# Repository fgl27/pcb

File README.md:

# pcb

This is a collection of PCBs prototypes for projects that I have created off participated.

If anything here help you enjoy it.

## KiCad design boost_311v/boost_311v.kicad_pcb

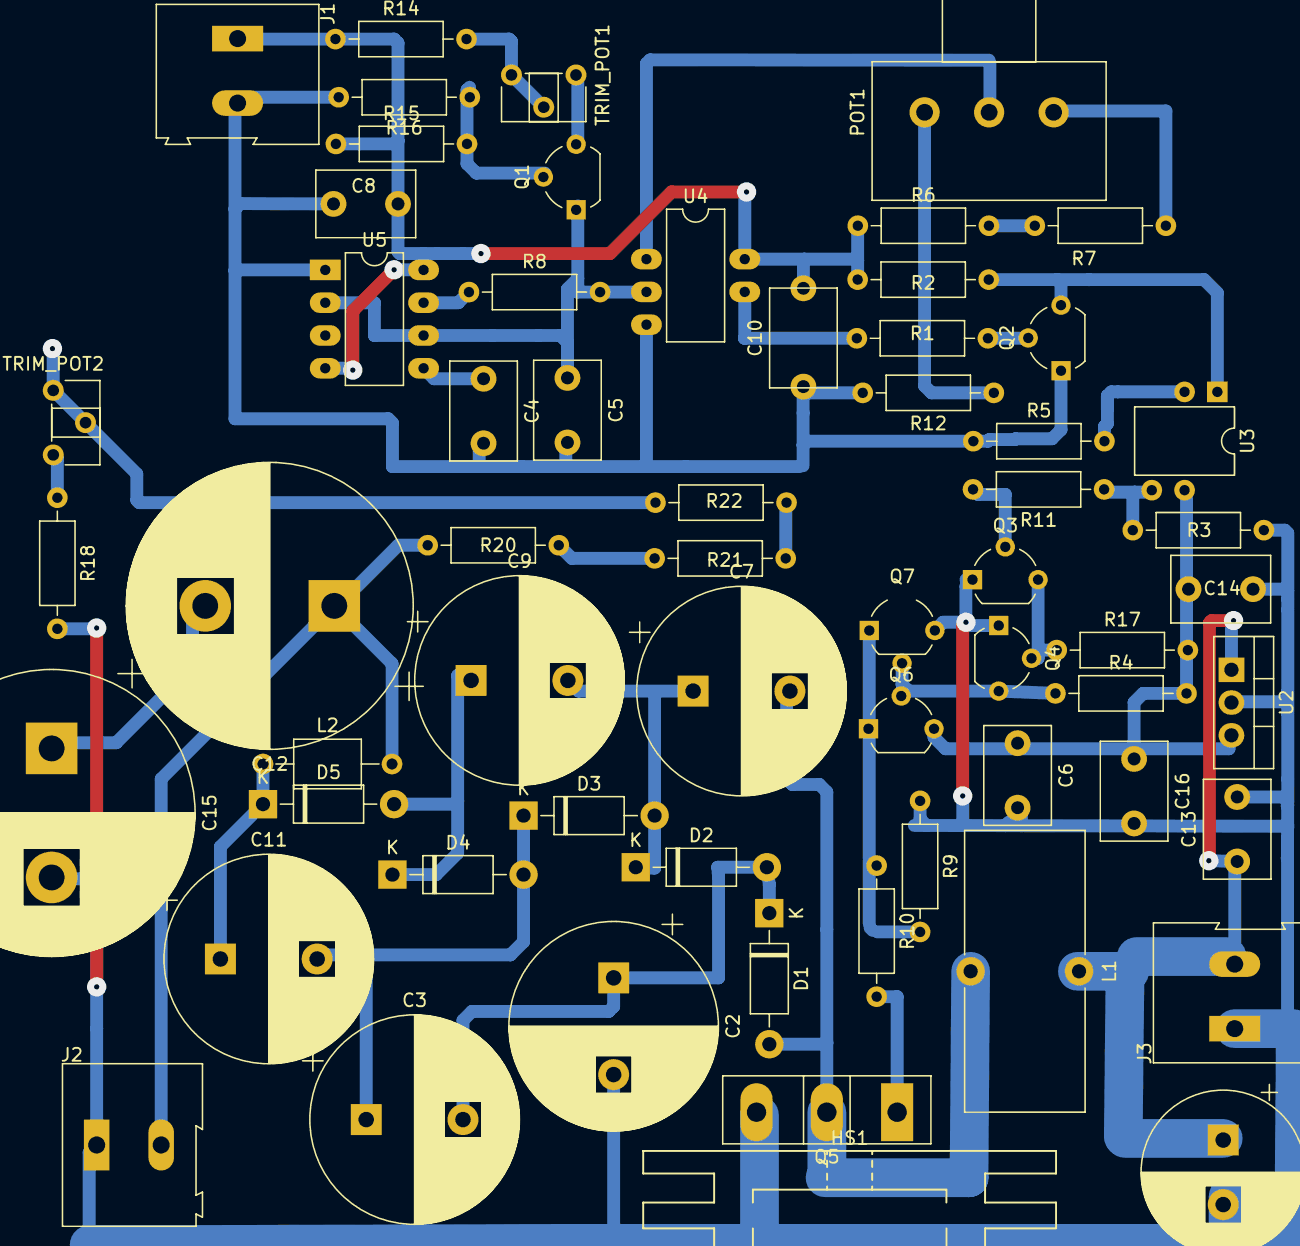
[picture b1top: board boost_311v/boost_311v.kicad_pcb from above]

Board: 2 copper layers, 61 parts (0 on the bottom side), 37 nets.

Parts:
C1: 100µF; CP_Radial_D12.5mm_P5.00mm
C2: 100µF; CP_Radial_D16.0mm_P7.50mm
C3, C7, C9, C11: 100µF_200V; CP_Radial_D16.0mm_P7.50mm
C4: 10nF; C_Disc_D7.5mm_W5.0mm_P5.00mm
C5: 500pF; C_Disc_D7.5mm_W5.0mm_P5.00mm
C6, C8, C10, C14, C16: 100nF; C_Disc_D7.5mm_W5.0mm_P5.00mm
C12, C15: 200µF_200V; CP_Radial_D22.0mm_P10.00mm_SnapIn
C13: 10µF; C_Disc_D7.5mm_W5.0mm_P5.00mm
D1, D2, D3, D4, D5: FR154; D_DO-41_SOD81_P10.16mm_Horizontal
HS1: Heatsink; Heatsink_Stonecold_HS-132_32x14mm_2xFixation1.5mm
J1: Vin_cnt; TerminalBlock_Altech_AK300-2_P5.00mm
J2: VO; TerminalBlock_Altech_AK300-2_P5.00mm
J3: Vin_boost; TerminalBlock_Altech_AK300-2_P5.00mm
L1: 20µH; L_Toroid_Vertical_L21.6mm_W9.1mm_P8.40mm_Bourns_5700
L2: 100µ; L_Axial_L5.0mm_D3.6mm_P10.00mm_Horizontal_Murata_BL01RN1A2A2
POT1: 200kΩ; Potentiometer_Alps_RK163_Single_Horizontal
Q1: BC556; TO-92_Wide
Q2, Q3, Q4: PN2222A; TO-92_Wide
Q5: IRFP260; TO-247-3_Vertical
Q6: 2N3904; TO-92_Wide
Q7: 2N3906; TO-92_Wide
R1, R2, R4, R14: 1kΩ; R_Axial_DIN0207_L6.3mm_D2.5mm_P10.16mm_Horizontal
R3, R8: 330Ω; R_Axial_DIN0207_L6.3mm_D2.5mm_P10.16mm_Horizontal
R5: 470Ω; R_Axial_DIN0207_L6.3mm_D2.5mm_P10.16mm_Horizontal
R6, R7, R16, R18: 100kΩ; R_Axial_DIN0207_L6.3mm_D2.5mm_P10.16mm_Horizontal
R9, R11, R15, R17: 10kΩ; R_Axial_DIN0207_L6.3mm_D2.5mm_P10.16mm_Horizontal
R10: 47Ω; R_Axial_DIN0207_L6.3mm_D2.5mm_P10.16mm_Horizontal
R12: 80kΩ; R_Axial_DIN0207_L6.3mm_D2.5mm_P10.16mm_Horizontal
R20, R21: 330kΩ; R_Axial_DIN0207_L6.3mm_D2.5mm_P10.16mm_Horizontal
R22: 220kΩ; R_Axial_DIN0207_L6.3mm_D2.5mm_P10.16mm_Horizontal
TRIM_POT1, TRIM_POT2: 22kΩ; Potentiometer_ACP_CA6-H2,5_Horizontal
U2: L7812; TO-220-3_Vertical
U3: 4N25; DIP-6_W7.62mm
U4: LF357; DIP-8_W7.62mm_LongPads
U5: NE555; DIP-8_W7.62mm_LongPads

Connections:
+12V: C8.1, C10.2, J1.2, R2.2, R6.1, R14.1, R15.1, U4.7, U5.4, U5.8
+24V: C1.1, C13.1, J3.2, L1.1, U2.1
/10%_VO: R22.2, TRIM_POT2.1, TRIM_POT2.2
/12V_L7812: C6.1, C14.1, C16.1, Q6.3, R4.2, R17.2, U2.3, U3.5
/F_Serra: C5.1, Q1.1, R8.2, U4.3, U5.2, U5.6
/MOS_Gate: Q6.1, Q7.1, R9.2, R10.1
/PWM: Q2.3, R2.1, U3.1
GND: C4.2, C5.2, C8.2, C10.1, J1.1, Q2.1, R5.1, R12.2, R16.2, U4.4, U5.1
GNDA: C1.2, C2.2, C6.2, C13.2, C14.2, C15.2, C16.2, J2.2, J3.1, Q3.1, Q4.1, Q5.3, Q7.3, R3.1, R9.1, R18.2, U2.2
unnamed: C2.1, C3.2, D1.2, D2.1
unnamed: C4.1, U5.5
unnamed: C7.1, C9.2, D2.2, D3.1
unnamed: C7.2, D1.1, L1.2, Q5.2
unnamed: C9.1, D4.2, D5.1
unnamed: C11.1, D5.2, L2.1
unnamed: C3.1, C11.2, D3.2, D4.1
unnamed: C12.1, J2.1, L2.2, R20.1
unnamed: C12.2, C15.1
unnamed: POT1.1, R7.2
unnamed: POT1.2, U4.2
unnamed: POT1.3, R12.1
unnamed: Q1.2, R15.2, R16.1
unnamed: Q1.3, TRIM_POT1.3
unnamed: Q2.2, R1.2
unnamed: Q3.2, R11.2
unnamed: Q3.3, Q4.2, R17.1
unnamed: Q4.3, Q6.2, Q7.2, R4.1
unnamed: Q5.1, R10.2
unnamed: R1.1, U4.6
unnamed: R5.2, U3.2
unnamed: R6.2, R7.1
unnamed: R8.1, U5.7
unnamed: R3.2, R11.1, U3.4
unnamed: R14.2, TRIM_POT1.1, TRIM_POT1.2
unnamed: R18.1, TRIM_POT2.3
unnamed: R20.2, R21.1
unnamed: R21.2, R22.1

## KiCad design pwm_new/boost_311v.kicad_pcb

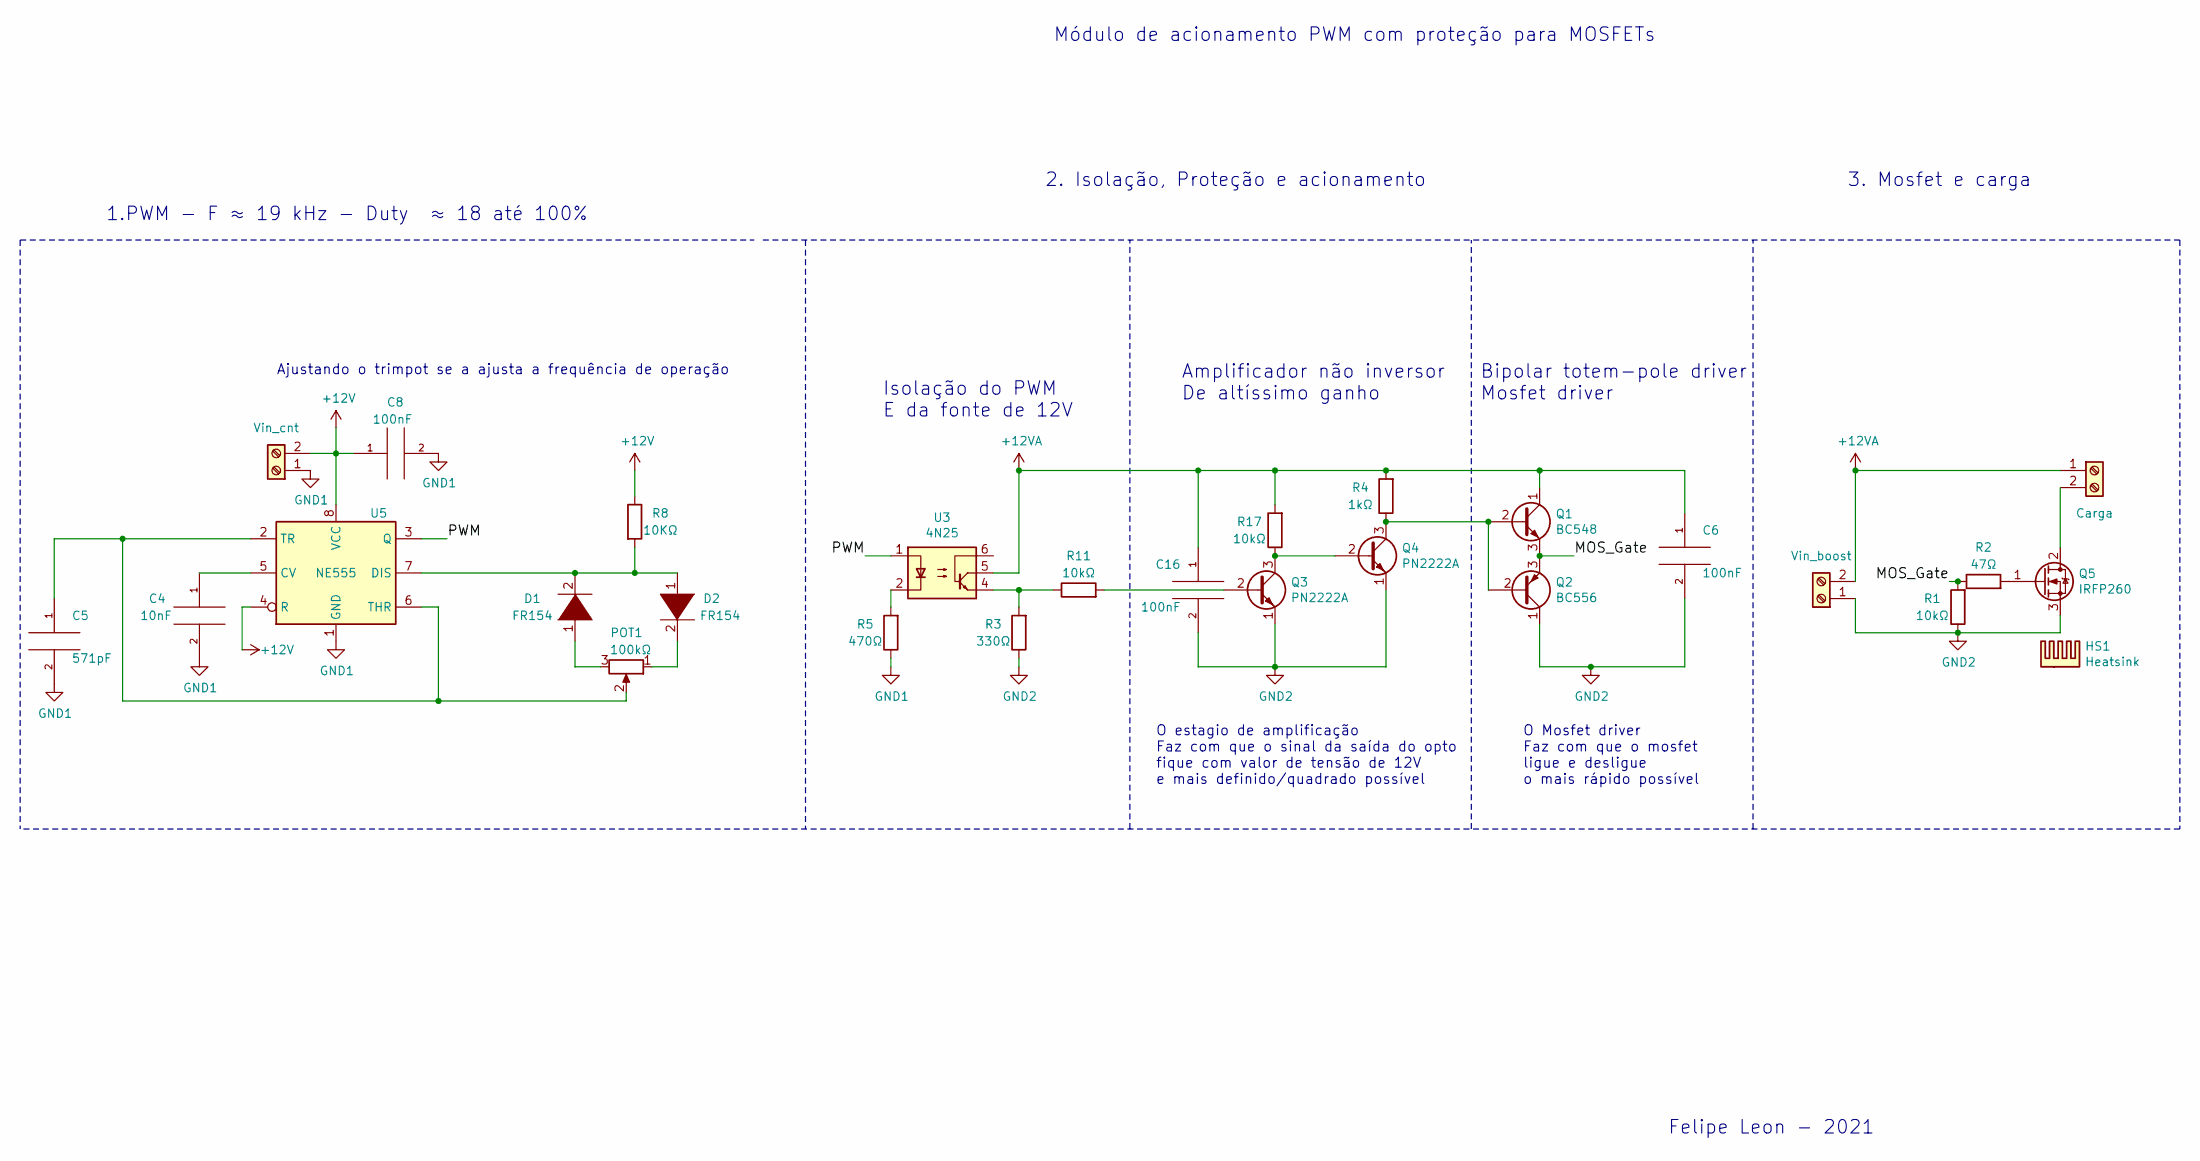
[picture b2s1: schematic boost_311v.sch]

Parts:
C4: 10nF; C_Disc_D7.5mm_W5.0mm_P5.00mm
C5: 571pF; C_Disc_D7.5mm_W5.0mm_P5.00mm
C6, C8, C16: 100nF; C_Disc_D7.5mm_W5.0mm_P5.00mm
D1, D2: FR154; D_DO-41_SOD81_P10.16mm_Horizontal
HS1: Heatsink; Heatsink_Stonecold_HS-132_32x14mm_2xFixation1.5mm
J1: Vin_cnt; TerminalBlock_Altech_AK300-2_P5.00mm
J2: Carga; TerminalBlock_Altech_AK300-2_P5.00mm
J3: Vin_boost; TerminalBlock_Altech_AK300-2_P5.00mm
POT1: 100kΩ; Potentiometer_Alps_RK163_Single_Horizontal
Q1: BC548; TO-92_Wide
Q2: BC556; TO-92_Wide
Q3, Q4: PN2222A; TO-92_Wide
Q5: IRFP260; TO-247-3_Vertical
R1, R11, R17: 10kΩ; R_Axial_DIN0207_L6.3mm_D2.5mm_P10.16mm_Horizontal
R2: 47Ω; R_Axial_DIN0207_L6.3mm_D2.5mm_P10.16mm_Horizontal
R3: 330Ω; R_Axial_DIN0207_L6.3mm_D2.5mm_P10.16mm_Horizontal
R4: 1kΩ; R_Axial_DIN0207_L6.3mm_D2.5mm_P10.16mm_Horizontal
R5: 470Ω; R_Axial_DIN0207_L6.3mm_D2.5mm_P10.16mm_Horizontal
R8: 10KΩ; R_Axial_DIN0207_L6.3mm_D2.5mm_P10.16mm_Horizontal
U3: 4N25; DIP-6_W7.62mm
U5: NE555; DIP-8_W7.62mm_LongPads

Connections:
+12V: C8.1, J1.2, R8.1, U5.4 (R), U5.8 (VCC)
+12VA: C6.1, C16.1, J2.1, J3.2, Q1.1 (C), R4.2, R17.2, U3.5
/MOS_Gate: Q1.3 (E), Q2.3 (E), R1.2, R2.1
/PWM: U3.1, U5.3 (Q)
GND1: C4.2, C5.2, C8.2, J1.1, R5.1, U5.1 (GND)
GND2: C6.2, C16.2, J3.1, Q2.1 (C), Q3.1 (E), Q4.1 (E), Q5.3 (S), R1.1, R3.1
unnamed: C4.1, U5.5 (CV)
unnamed: C5.1, POT1.2, U5.2 (TR), U5.6 (THR)
unnamed: D1.1 (K), POT1.3
unnamed: D1.2 (A), D2.1 (K), R8.2, U5.7 (DIS)
unnamed: D2.2 (A), POT1.1
unnamed: J2.2, Q5.2 (D)
unnamed: Q1.2 (B), Q2.2 (B), Q4.3 (C), R4.1
unnamed: Q3.2 (B), R11.2
unnamed: Q3.3 (C), Q4.2 (B), R17.1
unnamed: Q5.1 (G), R2.2
unnamed: R5.2, U3.2
unnamed: R3.2, R11.1, U3.4

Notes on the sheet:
1.PWM - F ≈ 19 kHz - Duty ≈ 18 até 100%
Ajustando o trimpot se a ajusta a frequência de operação
Felipe Leon - 2021
Isolação do PWM E da fonte de 12V
Amplificador não inversor De altíssimo ganho
Bipolar totem-pole driver Mosfet driver
O estagio de amplificação Faz com que o sinal da saída do opto fique com valor de tensão de 12V e mais definido/quadrado possível
O Mosfet driver Faz com que o mosfet ligue e desligue o mais rápido possível
3. Mosfet e carga
Módulo de acionamento PWM com proteção para MOSFETs
2. Isolação, Proteção e acionamento

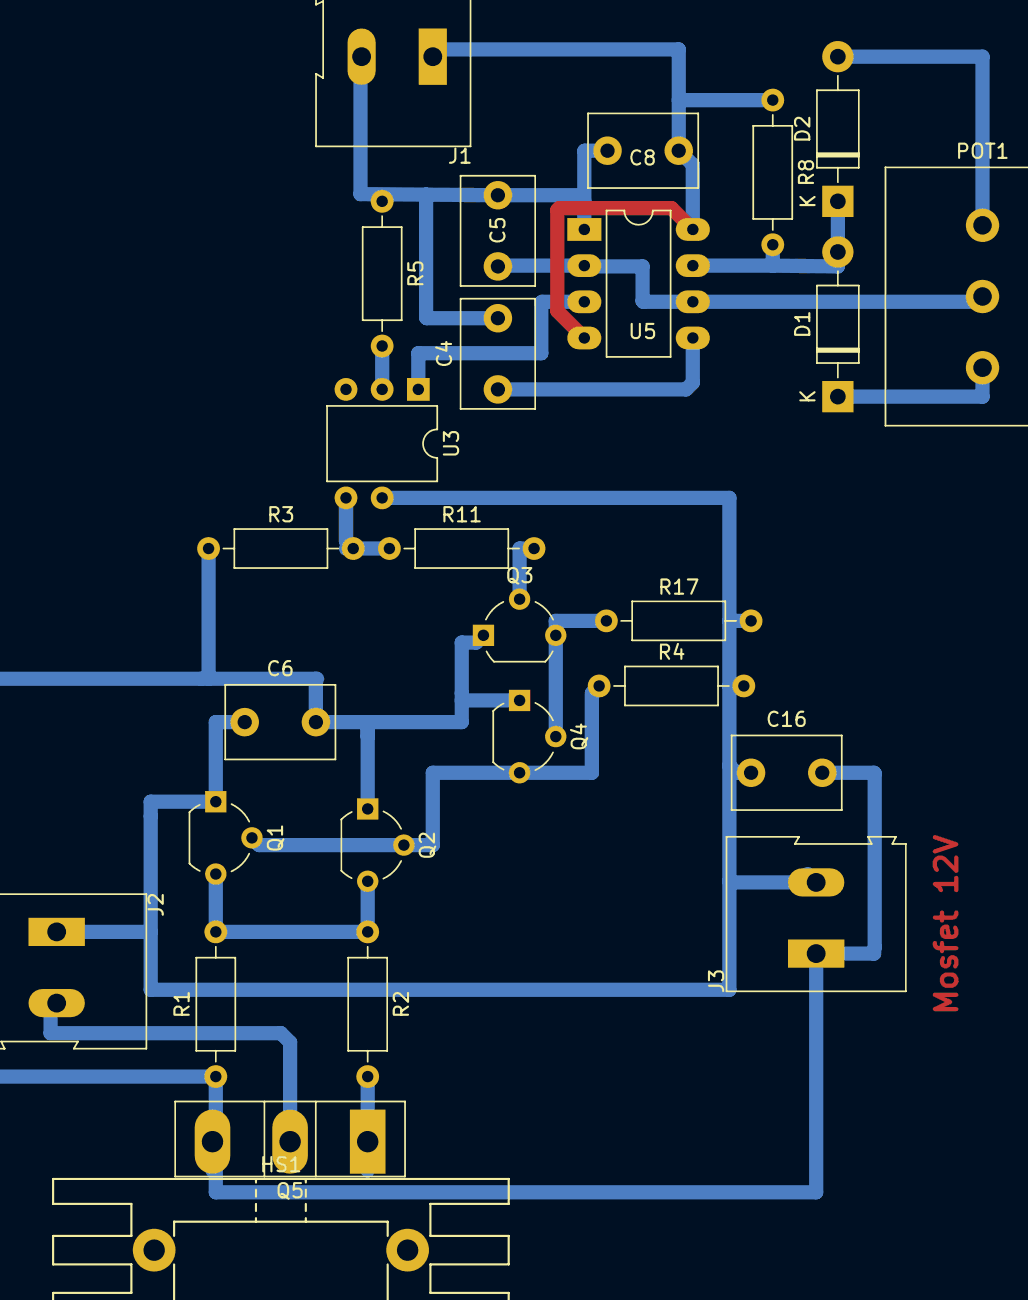
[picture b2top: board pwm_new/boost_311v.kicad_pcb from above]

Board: 2 copper layers, 27 parts (0 on the bottom side), 18 nets.

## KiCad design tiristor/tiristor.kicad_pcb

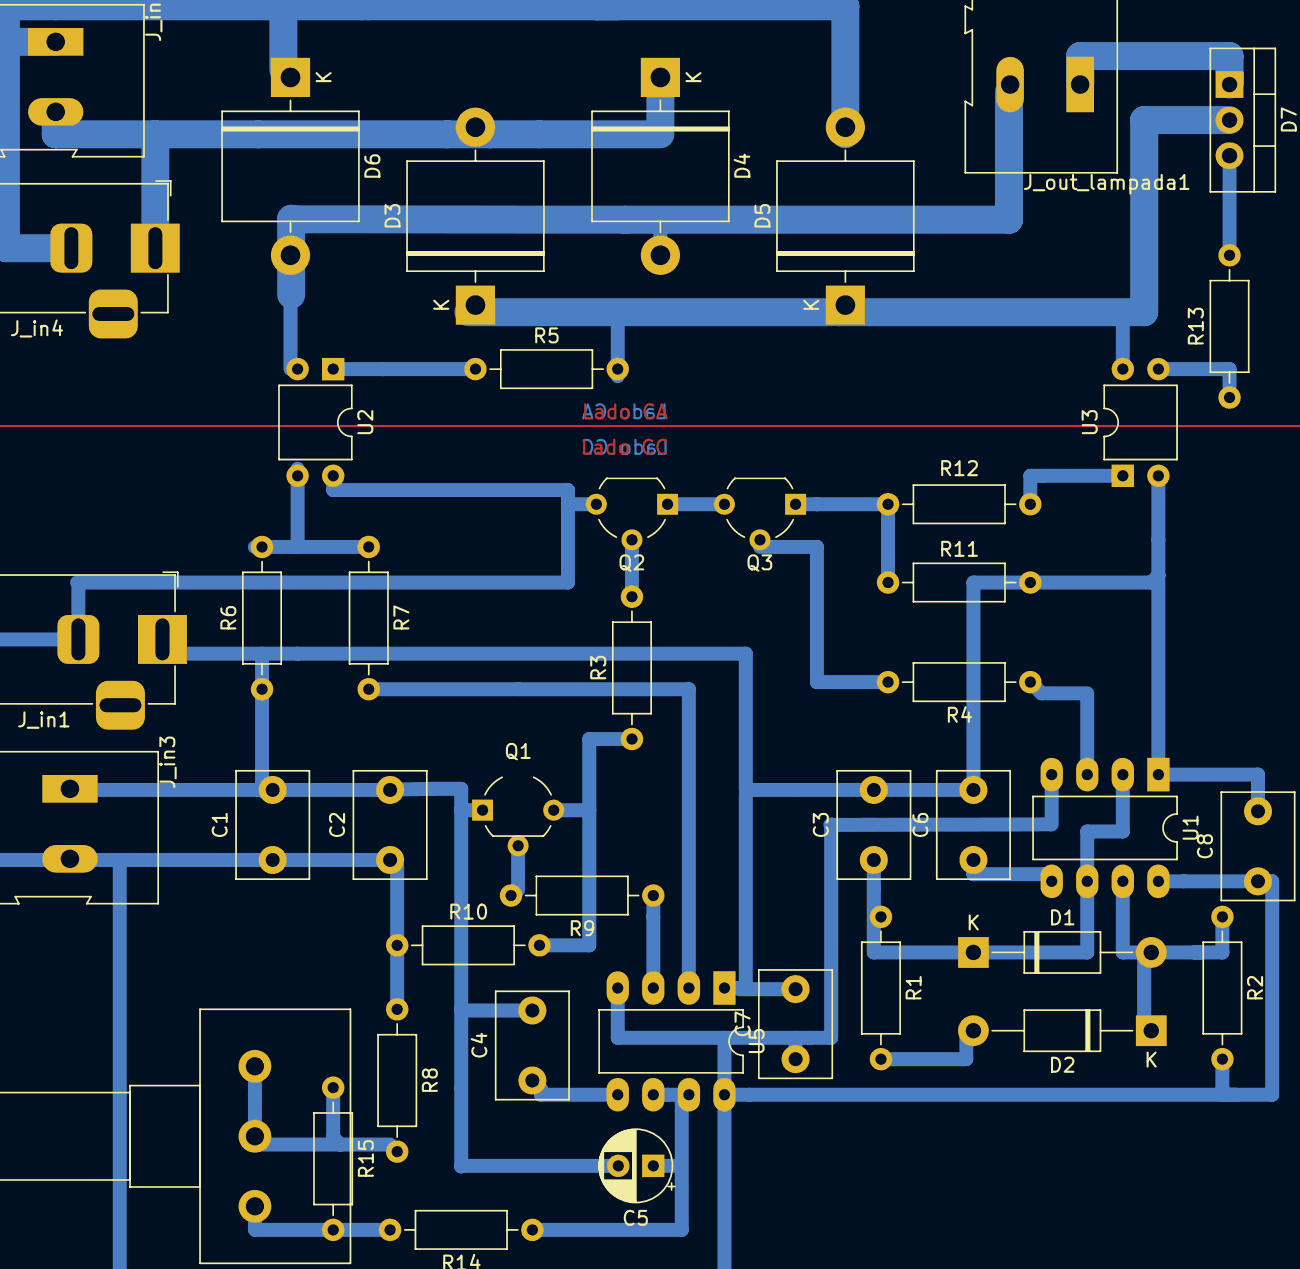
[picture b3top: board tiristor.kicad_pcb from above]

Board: 2 copper layers, 43 parts (0 on the bottom side), 29 nets.

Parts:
C1, C2, C7, C8: 100n; C_Disc_D7.5mm_W5.0mm_P5.00mm
C3: 4.7n; C_Disc_D7.5mm_W5.0mm_P5.00mm
C4, C6: 10n; C_Disc_D7.5mm_W5.0mm_P5.00mm
C5: 2.2u; CP_Radial_D5.0mm_P2.50mm
D1, D2: DIODE; D_DO-41_SOD81_P12.70mm_Horizontal
D3, D4, D5, D6: DIODE; D_5KP_P12.70mm_Horizontal
D7: BT151; TO-220-3_Vertical
J_in1, J_in4: Screw_Terminal_01x02; BarrelJack_Horizontal
J_in2, J_in3: Screw_Terminal_01x02; TerminalBlock_Altech_AK300-2_P5.00mm
J_out_lampada1: Screw_Terminal_01x02; TerminalBlock_Altech_AK300-2_P5.00mm
Q1, Q2, Q3: PN2222A; TO-92_Wide
R1: 2.2k; R_Axial_DIN0207_L6.3mm_D2.5mm_P10.16mm_Horizontal
R2, R5, R7, R12, R13: 1k; R_Axial_DIN0207_L6.3mm_D2.5mm_P10.16mm_Horizontal
R3, R4, R9: 22k; R_Axial_DIN0207_L6.3mm_D2.5mm_P10.16mm_Horizontal
R6: 40k; R_Axial_DIN0207_L6.3mm_D2.5mm_P10.16mm_Horizontal
R8: 150; R_Axial_DIN0207_L6.3mm_D2.5mm_P10.16mm_Horizontal
R10, R11: 470; R_Axial_DIN0207_L6.3mm_D2.5mm_P10.16mm_Horizontal
R14: 200; R_Axial_DIN0207_L6.3mm_D2.5mm_P10.16mm_Horizontal
R15: 6k(10||15k); R_Axial_DIN0207_L6.3mm_D2.5mm_P10.16mm_Horizontal
RV2: POT_5k; Potentiometer_Alps_RK163_Single_Horizontal
U1, U5: NE555; DIP-8_W7.62mm_LongPads
U2, U3: PC817; DIP-4_W7.62mm

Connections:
+12V: C1.1, C2.1, C7.1, C8.1, J_in1.2, J_in3.2, Q2.3, R2.2, R8.1, R10.1, U1.4, U1.8, U2.4, U5.4, U5.8
/+AC_Retificado: D3.2, D5.2, D7.2, R5.2, U3.4
/-AC_Retificado: D4.1, D6.1, J_out_lampada1.2, U2.2
/F_ataque: R4.1, U1.3
/F_out_AND: Q3.1, R11.1, R12.2
/F_out_PWM: R9.1, U5.3
/F_out_PWM_Align_right: Q1.3, R3.1, R10.2
AC: D5.1, D6.2, J_in2.2, J_in4.1
GND: C1.2, C2.2, C3.2, C4.2, C5.2, C6.2, C7.2, C8.2, J_in1.1, J_in3.1, Q1.1, R6.1, R11.2, U1.1, U3.2, U5.1
unnamed: C3.1, D1.2, R1.1, U1.2, U1.6
unnamed: C4.1, U5.5
unnamed: C5.1, R14.1, U5.6, U5.7
unnamed: C6.1, U1.5
unnamed: D1.1, D2.2, R2.1, U1.7
unnamed: D2.1, R1.2
unnamed: D3.1, D4.2, J_in2.1, J_in4.2
unnamed: D7.1, J_out_lampada1.1
unnamed: D7.3, R13.2
unnamed: Q1.2, R9.2
unnamed: Q2.1, Q3.3
unnamed: Q2.2, R3.2
unnamed: Q3.2, R4.2
unnamed: R5.1, U2.1
unnamed: R6.2, R7.1, U2.3
unnamed: R7.2, U5.2
unnamed: R12.1, U3.1
unnamed: R13.1, U3.3
unnamed: R14.2, R15.2, RV2.3
unnamed: R8.2, R15.1, RV2.1, RV2.2

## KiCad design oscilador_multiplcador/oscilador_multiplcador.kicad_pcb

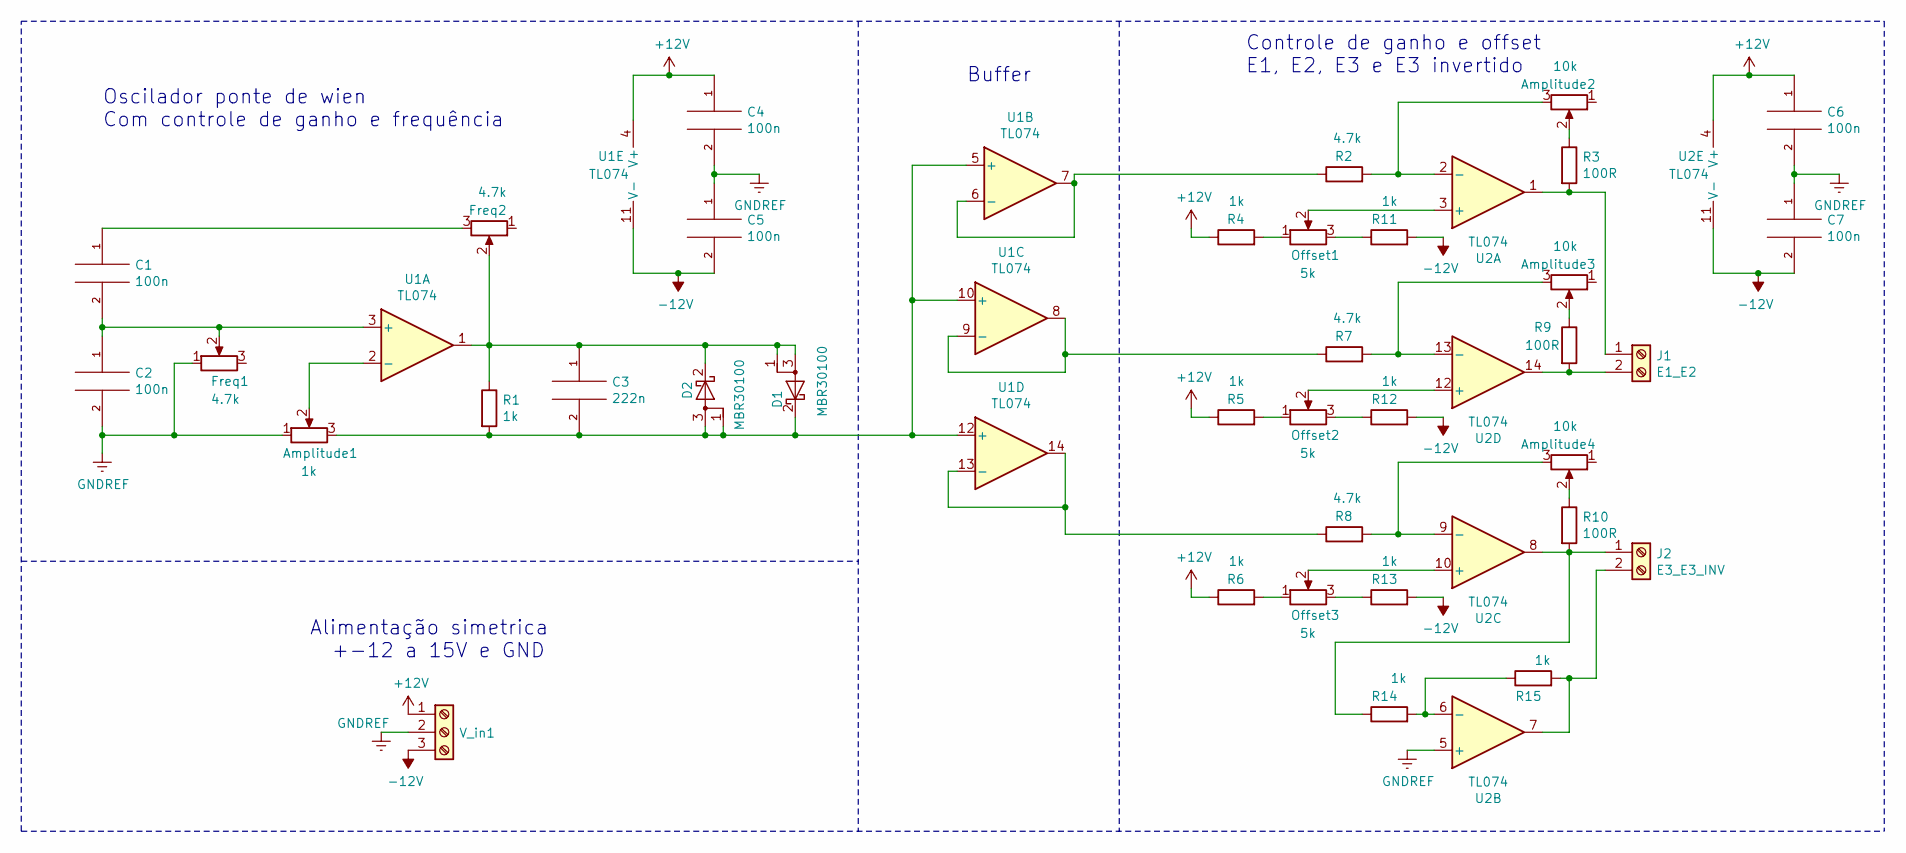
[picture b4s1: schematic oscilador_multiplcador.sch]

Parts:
Amplitude1: 1k; Potentiometer_ACP_CA9-H5_Horizontal
Amplitude2, Amplitude3, Amplitude4: 10k; Potentiometer_Alps_RK163_Single_Horizontal
C1, C2, C4, C5, C6, C7: 100n; C_Disc_D7.5mm_W5.0mm_P7.50mm
C3: 222n; C_Rect_L13.0mm_W5.0mm_P10.00mm_FKS3_FKP3_MKS4
D1, D2: MBR30100; TO-220-3_Vertical
Freq1, Freq2: 4.7k; Potentiometer_ACP_CA9-H5_Horizontal
J1: E1_E2; TerminalBlock_Altech_AK300-2_P5.00mm
J2: E3_E3_INV; TerminalBlock_Altech_AK300-2_P5.00mm
Offset1, Offset2, Offset3: 5k; Potentiometer_Alps_RK163_Single_Horizontal
R1, R4, R5, R6, R11, R12, R13, R14, R15: 1k; R_Axial_DIN0207_L6.3mm_D2.5mm_P15.24mm_Horizontal
R2, R7, R8: 4.7k; R_Axial_DIN0207_L6.3mm_D2.5mm_P15.24mm_Horizontal
R3: 100R; R_Axial_DIN0207_L6.3mm_D2.5mm_P10.16mm_Horizontal
R9, R10: 100R; R_Axial_DIN0207_L6.3mm_D2.5mm_P15.24mm_Horizontal
U1, U2: TL074; DIP-14_W7.62mm
V_in1: Screw_Terminal_01x03; TerminalBlock_Altech_AK300-3_P5.00mm

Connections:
+12V: C4.1, C6.1, R4.1, R5.1, R6.1, U1.4 (V+), U2.4 (V+), V_in1.1
-12V: C5.2, C7.2, R11.2, R12.2, R13.2, U1.11 (V-), U2.11 (V-), V_in1.3
GNDREF: Amplitude1.1, C2.2, C4.2, C5.1, C6.2, C7.1, Freq1.1, U2.5 (+), V_in1.2
unnamed: Amplitude1.2, U1.2 (-)
unnamed: Amplitude1.3, C3.2, D1.1 (A), D1.3 (A), D2.2 (K), R1.2, U1.5 (+), U1.10 (+), U1.12 (+)
unnamed: Amplitude2.2, R3.1
unnamed: Amplitude2.3, R2.2, U2.2 (-)
unnamed: Amplitude3.2, R9.1
unnamed: Amplitude3.3, R7.2, U2.13 (-)
unnamed: Amplitude4.2, R10.1
unnamed: Amplitude4.3, R8.2, U2.9 (-)
unnamed: C1.1, Freq2.3
unnamed: C1.2, C2.1, Freq1.2, U1.3 (+)
unnamed: C3.1, D1.2 (K), D2.1 (A), D2.3 (A), Freq2.2, R1.1, U1.1
unnamed: J1.1, R3.2, U2.1
unnamed: J1.2, R9.2, U2.14
unnamed: J2.1, R10.2, R14.1, U2.8
unnamed: J2.2, R15.2, U2.7
unnamed: Offset1.1, R4.2
unnamed: Offset1.2, U2.3 (+)
unnamed: Offset1.3, R11.1
unnamed: Offset2.1, R5.2
unnamed: Offset2.2, U2.12 (+)
unnamed: Offset2.3, R12.1
unnamed: Offset3.1, R6.2
unnamed: Offset3.2, U2.10 (+)
unnamed: Offset3.3, R13.1
unnamed: R2.1, U1.6 (-), U1.7
unnamed: R7.1, U1.8, U1.9 (-)
unnamed: R8.1, U1.13 (-), U1.14
unnamed: R14.2, R15.1, U2.6 (-)

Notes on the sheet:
Oscilador ponte de wien Com controle de ganho e frequência
Buffer
Controle de ganho e offset E1, E2, E3 e E3 invertido
Alimentação simetrica +-12 a 15V e GND

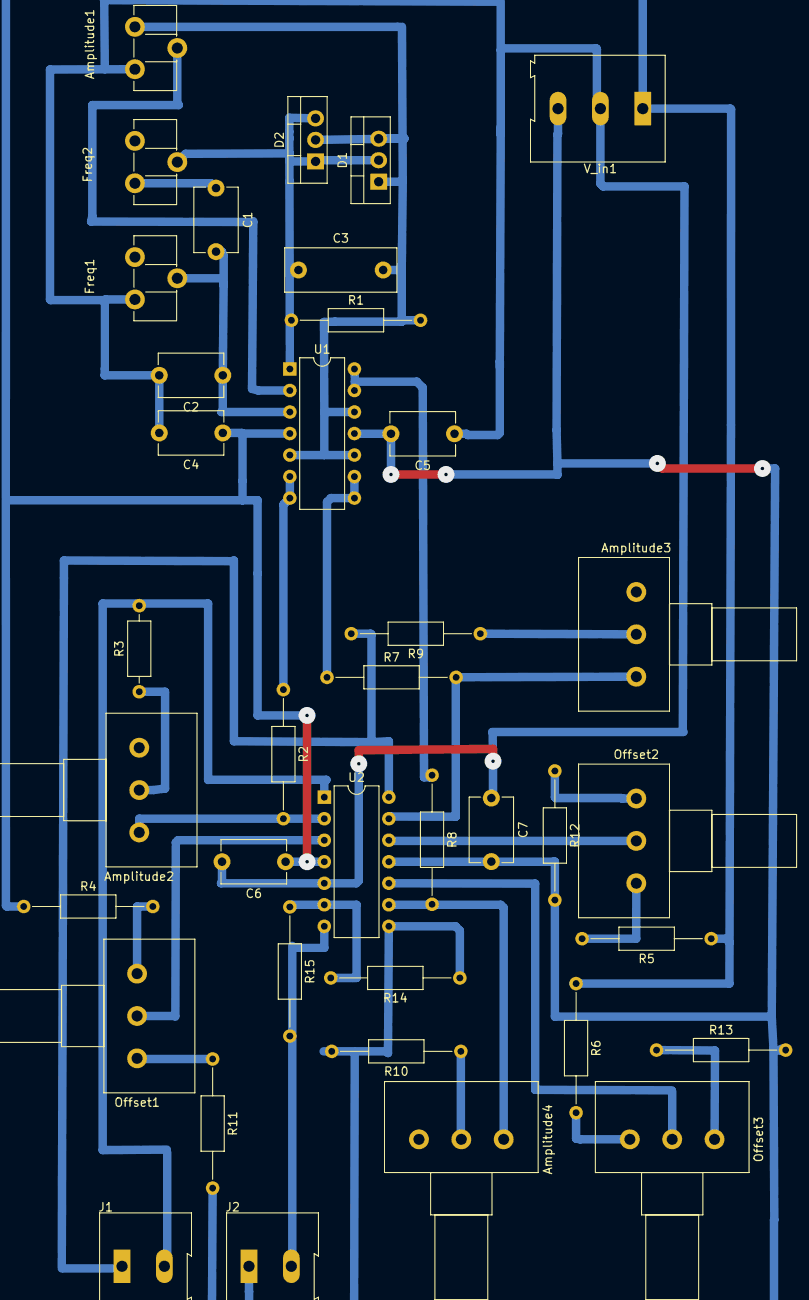
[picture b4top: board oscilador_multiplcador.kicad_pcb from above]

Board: 2 copper layers, 38 parts (0 on the bottom side), 31 nets.

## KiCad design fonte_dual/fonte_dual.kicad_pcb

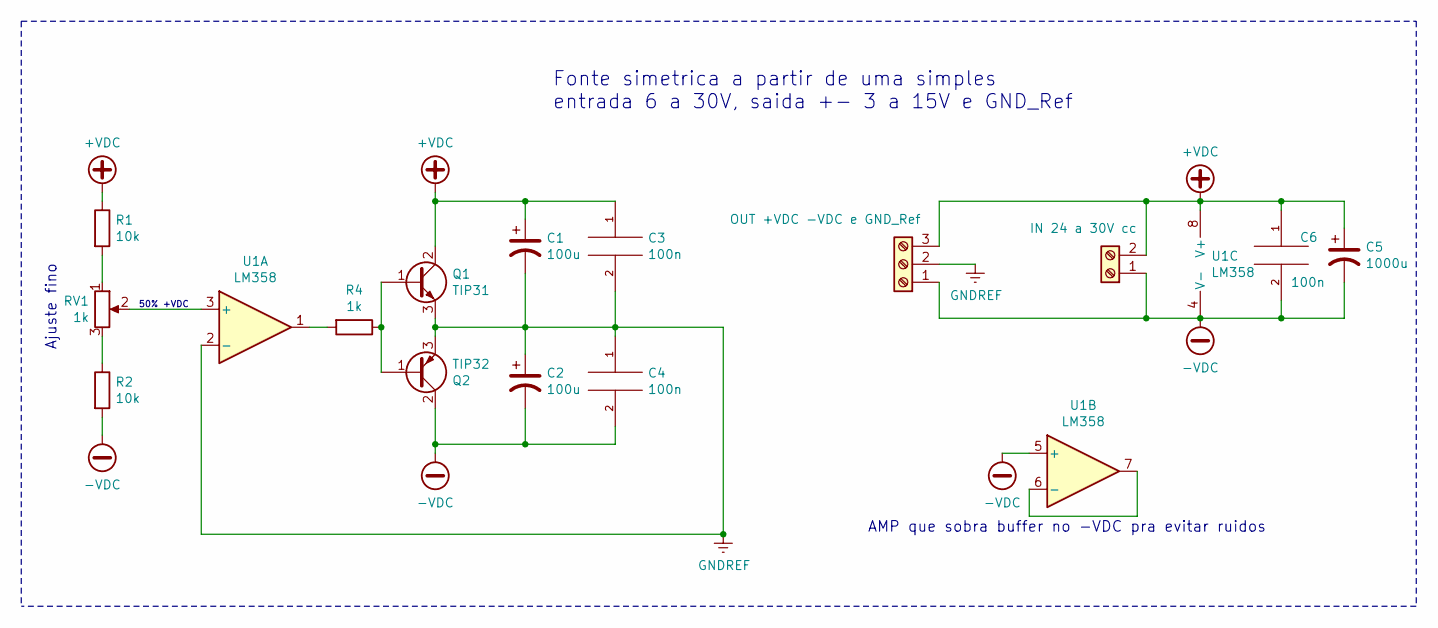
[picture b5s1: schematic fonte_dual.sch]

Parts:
C1, C2: 100u; CP_Radial_D5.0mm_P2.00mm
C3, C4, C6: 100n; C_Disc_D5.0mm_W2.5mm_P5.00mm
C5: 1000u; CP_Radial_D8.0mm_P5.00mm
J1: IN 24 a 30V cc; BarrelJack_Horizontal
J2: OUT +VDC -VDC e GND_Ref; Altech_AK300_1x03_P5.00mm_45-Degree
Q1: TIP31; TO-220-3_Vertical
Q2: TIP32; TO-220-3_Vertical
R1, R2: 10k; R_Axial_DIN0309_L9.0mm_D3.2mm_P12.70mm_Horizontal
R4: 1k; R_Axial_DIN0309_L9.0mm_D3.2mm_P12.70mm_Horizontal
RV1: 1k; Potentiometer_ACP_CA9-V10_Vertical
U1: LM358; DIP-8_W7.62mm

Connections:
+VDC: C1.1, C3.1, C5.1, C6.1, J1.2, J2.3, Q1.2 (C), R1.1, U1.8 (V+)
-VDC: C2.2, C4.2, C5.2, C6.2, J1.1, J2.1, Q2.2 (C), R2.2, U1.4 (V-), U1.5 (+)
GNDREF: C1.2, C2.1, C3.2, C4.1, J2.2, Q1.3 (E), Q2.3 (E), U1.2 (-)
unnamed: Q1.1 (B), Q2.1 (B), R4.1
unnamed: R1.2, RV1.1
unnamed: R2.1, RV1.3
unnamed: R4.2, U1.1
unnamed: RV1.2, U1.3 (+)
unnamed: U1.6 (-), U1.7

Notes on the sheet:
Fonte simetrica a partir de uma simples entrada 6 a 30V, saida +- 3 a 15V e GND_Ref
AMP que sobra buffer no -VDC pra evitar ruidos
Ajuste fino
50% +VDC

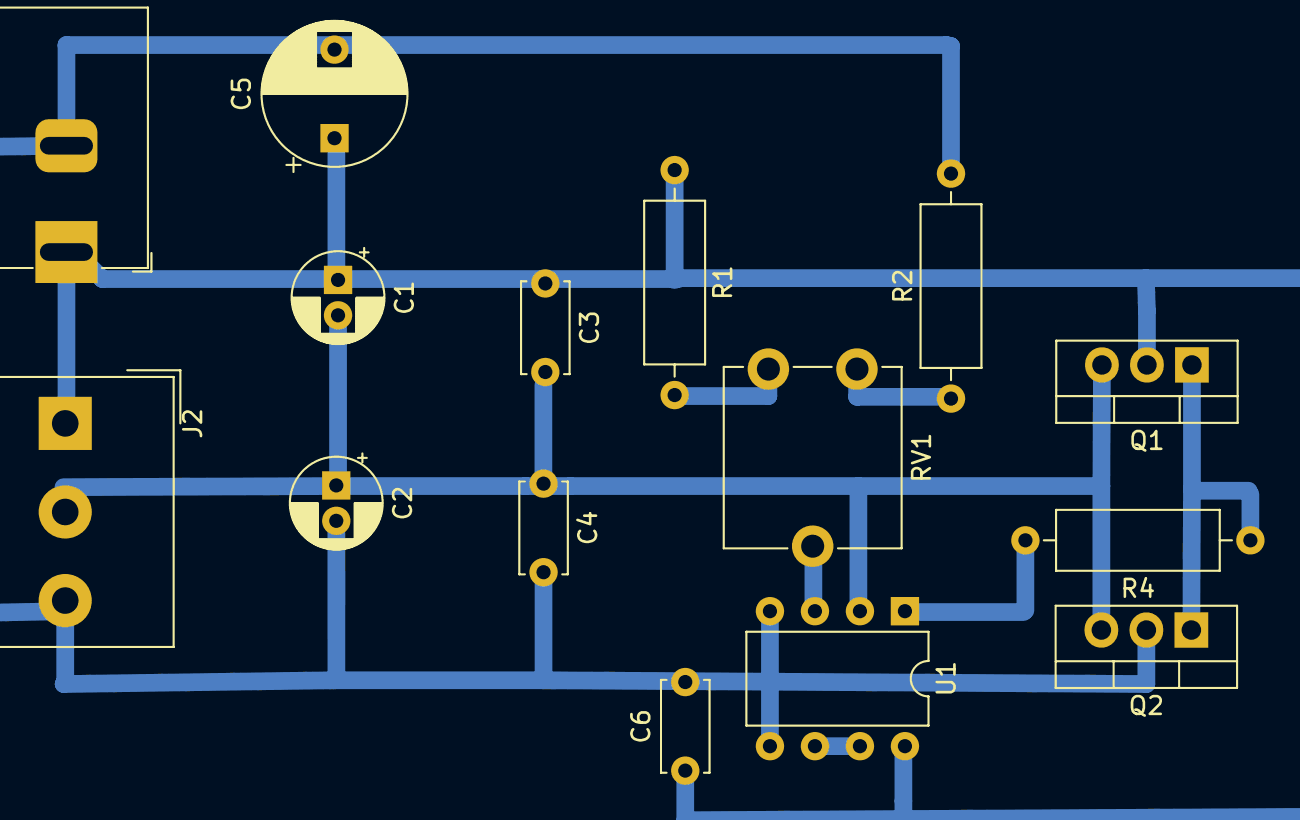
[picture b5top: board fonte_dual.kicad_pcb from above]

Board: 2 copper layers, 15 parts (0 on the bottom side), 9 nets.

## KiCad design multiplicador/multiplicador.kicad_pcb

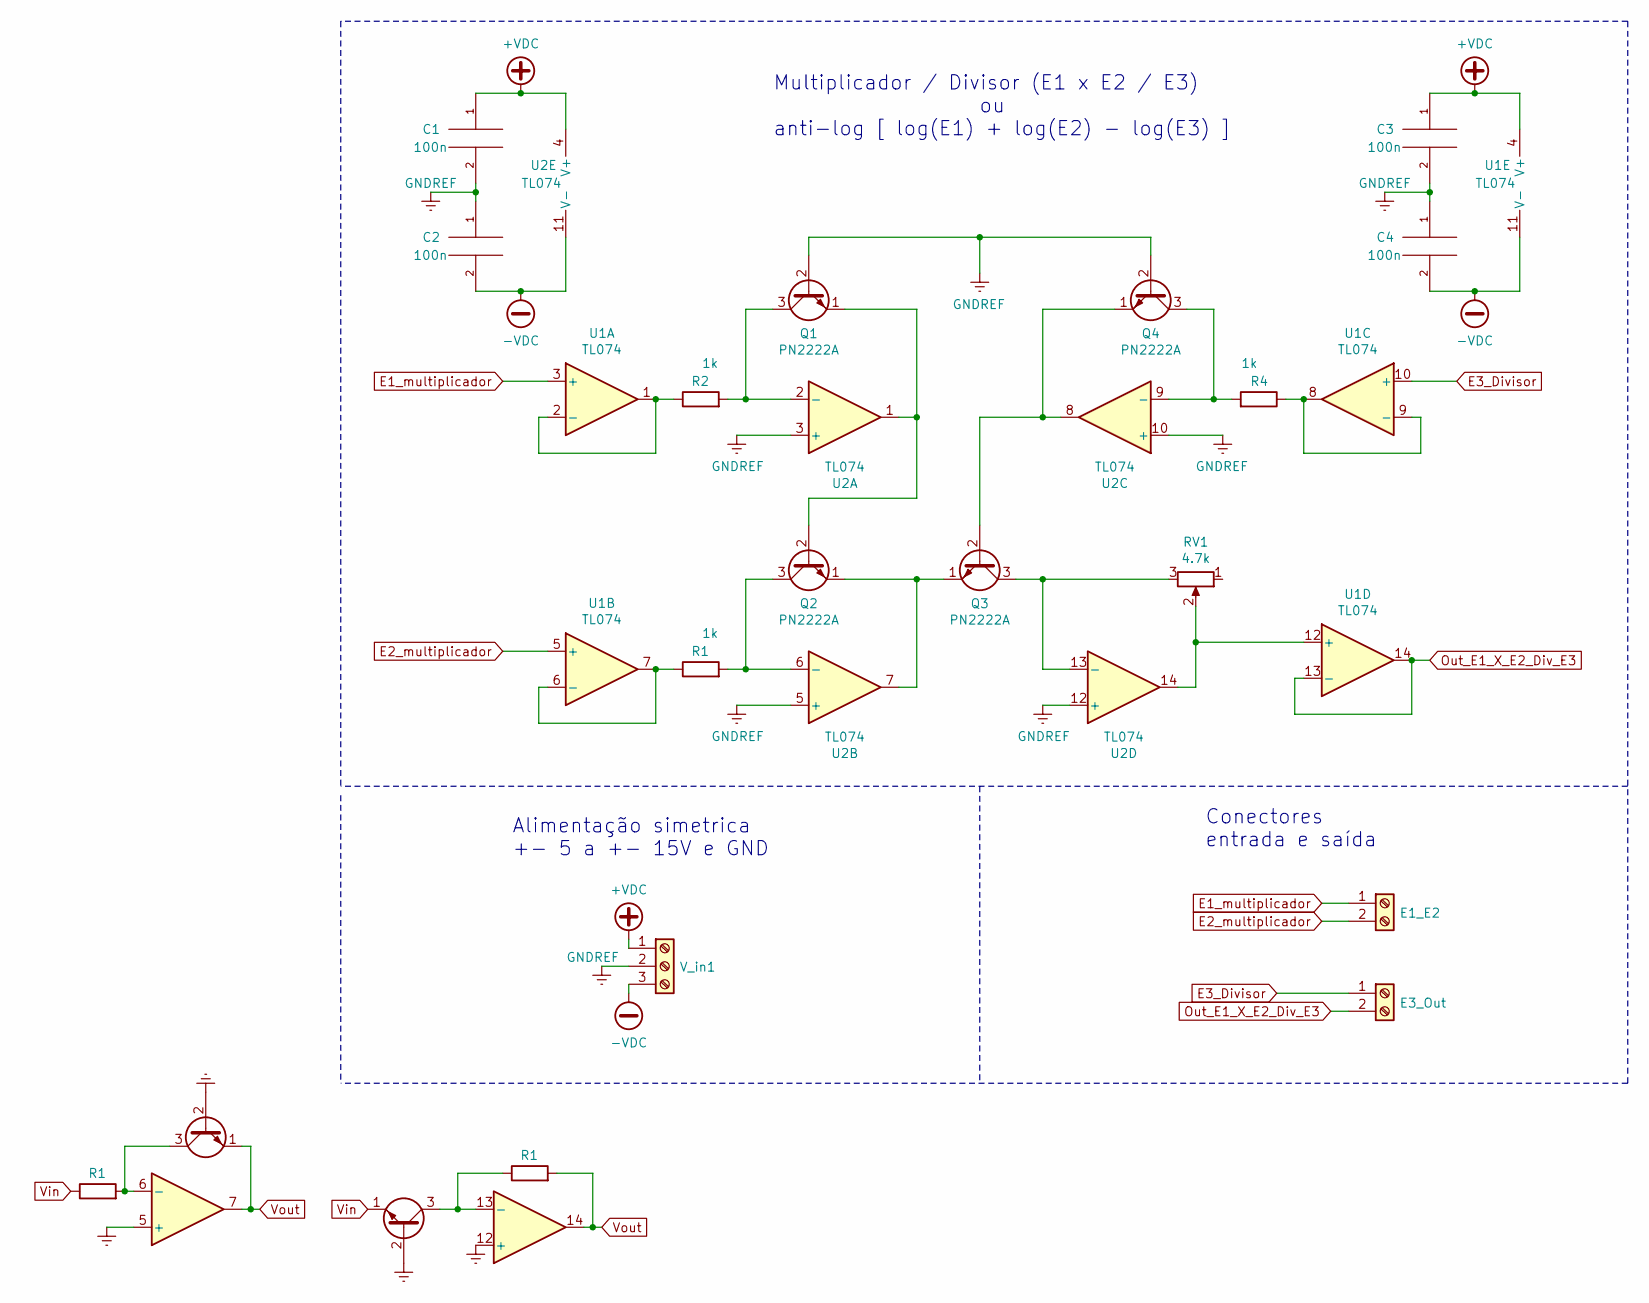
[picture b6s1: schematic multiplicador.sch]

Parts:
C1, C2: 100n; C_Disc_D7.5mm_W5.0mm_P7.50mm
C3, C4: 100n; C_Disc_D7.5mm_W5.0mm_P10.00mm
J1: E1_E2; TerminalBlock_Altech_AK300-2_P5.00mm
J2: E3_Out; TerminalBlock_Altech_AK300-2_P5.00mm
Q1, Q2, Q3, Q4: PN2222A; TO-92_Wide
R1, R4: 1k; R_Axial_DIN0309_L9.0mm_D3.2mm_P12.70mm_Horizontal
R2: 1k; R_Axial_DIN0207_L6.3mm_D2.5mm_P15.24mm_Horizontal
RV1: 4.7k; Potentiometer_ACP_CA9-H5_Horizontal
U1, U2: TL074; DIP-14_W7.62mm
V_in1: Screw_Terminal_01x03; TerminalBlock_Altech_AK300-3_P5.00mm

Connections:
+VDC: C1.1, C3.1, U1.4 (V+), U2.4 (V+), V_in1.1
-VDC: C2.2, C4.2, U1.11 (V-), U2.11 (V-), V_in1.3
E1_multiplicador: J1.1, U1.3 (+)
E2_multiplicador: J1.2, U1.5 (+)
E3_Divisor: J2.1, U1.10 (+)
GNDREF: C1.2, C2.1, C3.2, C4.1, Q1.2 (B), Q4.2 (B), U2.3 (+), U2.5 (+), U2.10 (+), U2.12 (+), V_in1.2
unnamed: Q1.1 (E), Q2.2 (B), U2.1
unnamed: Q1.3 (C), R2.2, U2.2 (-)
unnamed: Q2.1 (E), Q3.1 (E), U2.7
unnamed: Q2.3 (C), R1.2, U2.6 (-)
unnamed: Q3.2 (B), Q4.1 (E), U2.8
unnamed: Q3.3 (C), RV1.3, U2.13 (-)
unnamed: Q4.3 (C), R4.2, U2.9 (-)
unnamed: R1.1, U1.6 (-), U1.7
unnamed: R2.1, U1.1, U1.2 (-)
unnamed: R4.1, U1.8, U1.9 (-)
unnamed: RV1.2, U1.12 (+), U2.14
Out_E1_X_E2_Div_E3: J2.2, U1.13 (-), U1.14

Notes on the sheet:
Multiplicador / Divisor (E1 x E2 / E3) ou anti-log [ log(E1) + log(E2) - log(E3) ]
Conectores entrada e saída
Alimentação simetrica +- 5 a +- 15V e GND

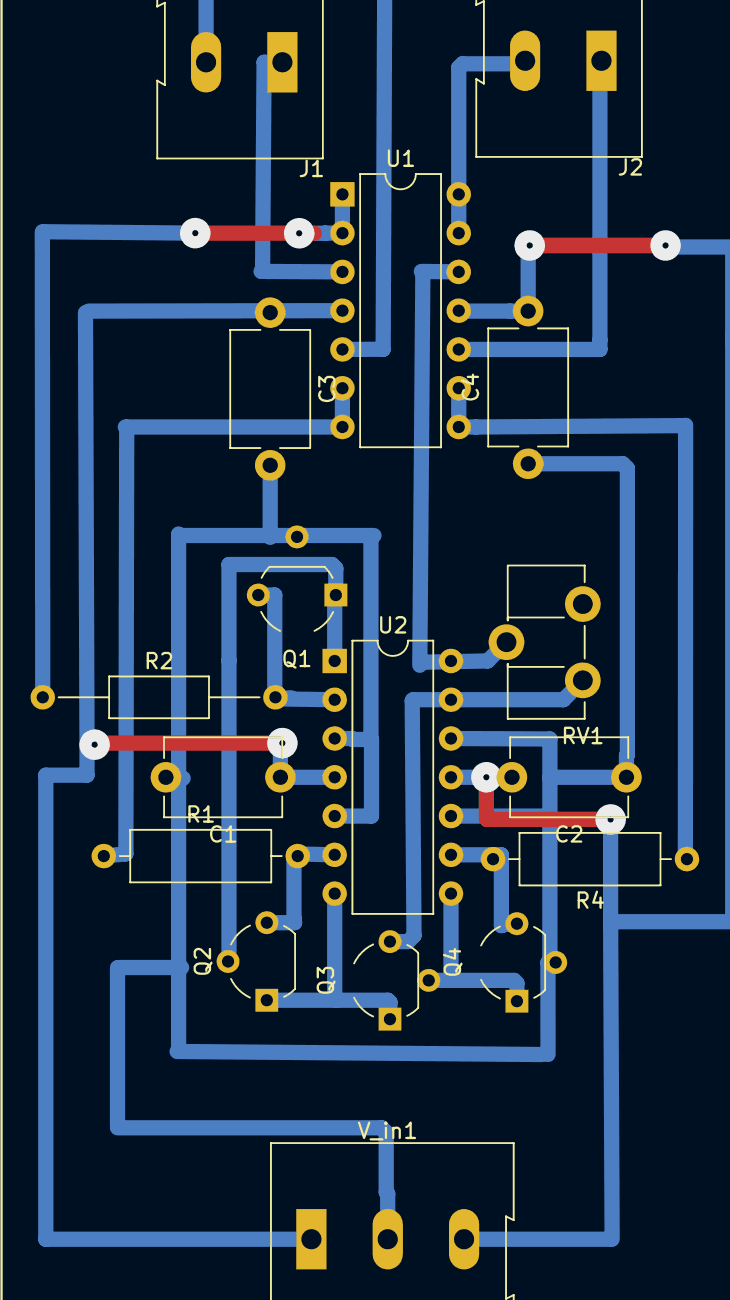
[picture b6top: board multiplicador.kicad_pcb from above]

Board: 2 copper layers, 17 parts (0 on the bottom side), 18 nets.
